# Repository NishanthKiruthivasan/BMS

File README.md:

# 🔋 Li-Ion Battery Charging Module with MCP73831

This project is a compact and reliable **single-cell Li-Ion/Li-Po battery charging board** using the **MCP73831T-2ACI/OT** linear charger IC. Designed for prototyping, IoT devices, and embedded systems requiring safe and simple battery charging from a 5V USB or adapter input.

---

## 📦 Features

- ✅ Input overvoltage and surge protection (TVS diode + fuse)
- ✅ Single-cell Li-Ion/Li-Po battery charging (4.2V, 500 mA)
- ✅ Charging status LED indicator (ON during charging, OFF when fully charged)
- ✅ Clean and simple 2-layer PCB design
- ✅ Output connector for system power
- ✅ Mounting holes and large battery cutout for easy integration

---

## ⚙️ Technical Specifications

| Parameter           | Value                   |
|--------------------|-------------------------|
| Charging IC        | MCP73831T-2ACI/OT       |
| Input Voltage      | 5V DC                   |
| Charging Current   | 500 mA (set via 2 kΩ resistor) |
| Battery Voltage    | 3.7V Nominal (4.2V max) |
| Capacitors         | 10µF & 4.7µF Ceramic    |
| Protections        | Fuse, TVS Diode         |

---

## 🧩 Schematic & PCB

The design is created using **KiCad** and includes:
- Complete schematic (.sch)
- PCB layout (.kicad_pcb)
- Gerber files for fabrication
- Bill of Materials (BOM)

---

## 🛡️ Battery Protection

> ⚠️ **Note**: This board does **not include battery protection** circuitry.  
Use **protected Li-Ion cells** or add an external **battery protection module** (e.g., DW01 + FS8205A) to ensure safe operation.

---

## 🖼️ Preview

### 📷 PCB Layout (Top View)

### 📄 Schematic PDF
[View Schematic PDF](NK_BMS_Schematic.pdf)

---

## 📁 License

This project is licensed under the **MIT License**.  
Feel free to use, modify, and distribute with attribution.

---

## 🤝 Contributions

Pull requests and suggestions are welcome!  
Feel free to open issues for improvements or bugs.

---

## 📧 Contact

Created by **Nishanth Kiruthivasan**  
📬 nishvask@gmail.com | kiruthivasan.n@northeastern.edu

🔗 [Website](https://nishanthkiruthivasan.carrd.co/)

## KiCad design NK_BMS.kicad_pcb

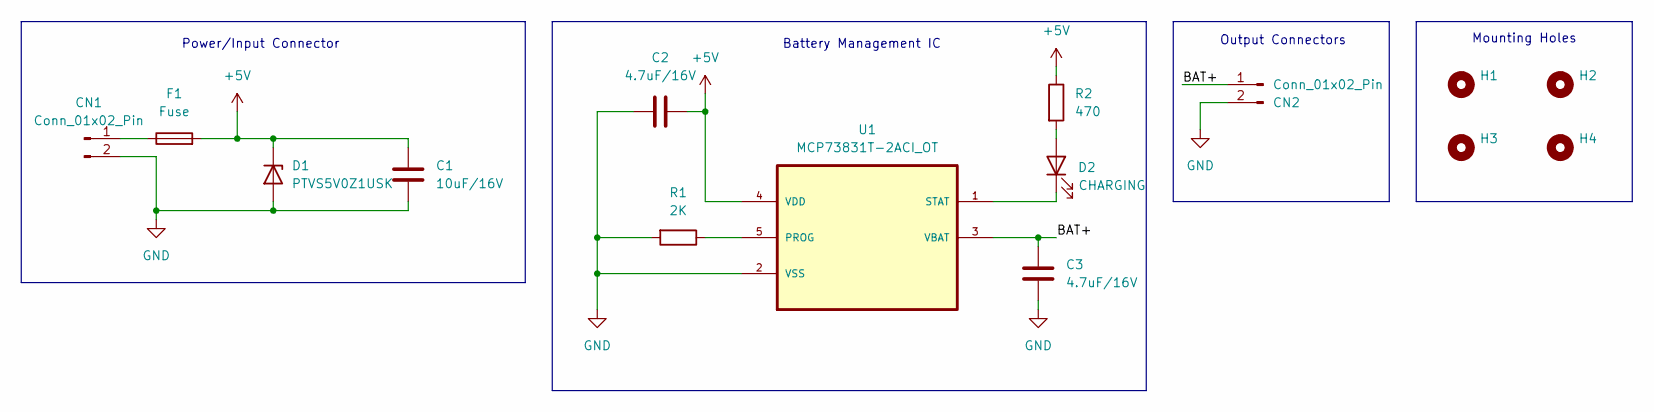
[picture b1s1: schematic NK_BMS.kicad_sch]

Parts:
C1: 10uF/16V; C_0805_2012Metric
C2, C3: 4.7uF/16V; C_0805_2012Metric
CN1: Conn_01x02_Pin; BarrelJack_CUI_PJ-063AH_Horizontal
CN2: Conn_01x02_Pin; BatteryHolder_Bulgin_BX0034_1xAAA
D1: PTVS5V0Z1USK; Nexperia_DSN1608-2_1.6x0.8mm
D2: CHARGING; LED_0805_2012Metric
F1: Fuse; Fuse_BelFuse_0ZRE0005FF_L8.3mm_W3.8mm
H1, H2, H3, H4: MountingHole; MountingHole_2.1mm
R1: 2K; R_0805_2012Metric
R2: 470; R_0805_2012Metric
U1: MCP73831T-2ACI_OT; SOT-23-5_HandSoldering; MPN MCP73831T-2ACI/OT

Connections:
+5V: C1.2, C2.2, D1.1 (K), F1.2, R2.1, U1.4 (VDD)
/BAT+: C3.2, CN2.1, U1.3 (VBAT)
GND: C1.1, C2.1, C3.1, CN1.2, CN2.2, D1.2 (A), R1.2, U1.2 (VSS)
unnamed: CN1.1, F1.1
unnamed: D2.2 (A), R2.2
unnamed: D2.1 (K), U1.1 (STAT)
unnamed: R1.1, U1.5 (PROG)

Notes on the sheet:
Mounting Holes
Power/Input Connector
Battery Management IC
Output Connectors

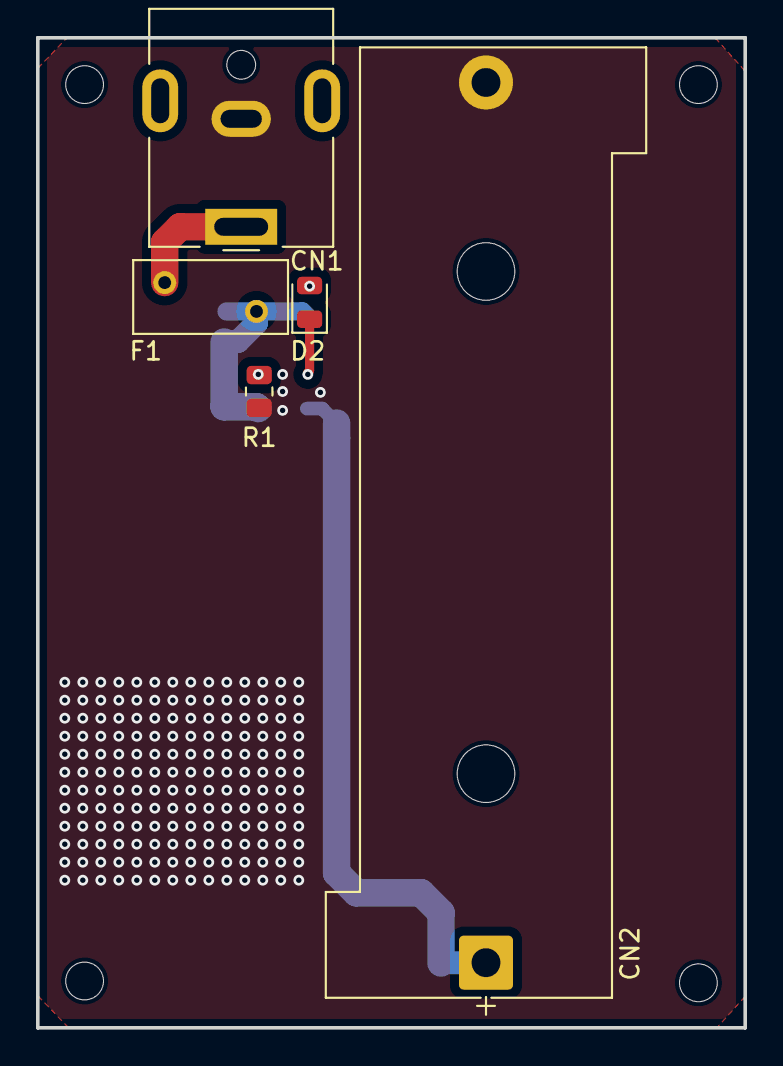
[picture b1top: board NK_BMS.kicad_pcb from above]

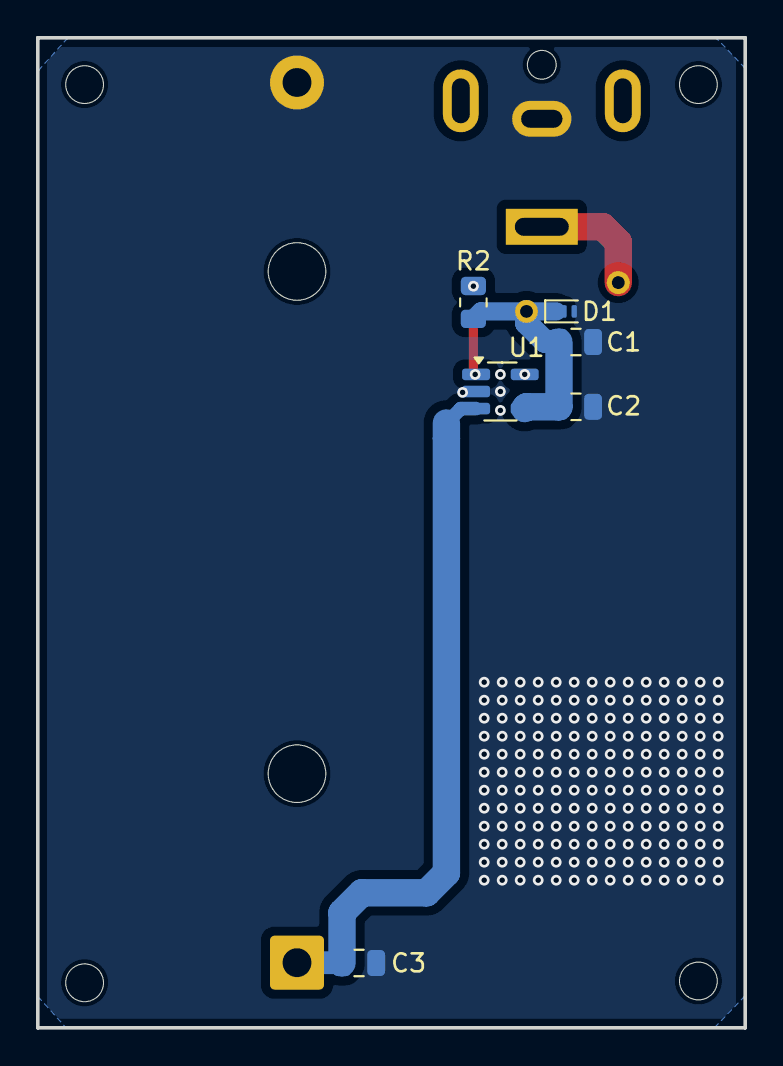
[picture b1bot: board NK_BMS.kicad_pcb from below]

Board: 2 copper layers, 39.3 x 55.0 mm, 15 parts (6 on the bottom side), 7 nets.

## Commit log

2025-06-26 Update README.md
    Added a Readme
2025-06-26 Added the project files
2025-06-26 Update README.md
    Added Schematic PDF link
2025-10-29 Update portfolio link to website
